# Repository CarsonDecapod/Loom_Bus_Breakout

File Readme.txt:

The Bus Breakout is a board for the Loom Prototyping Platform
It connects to one of the top or bottom ports of the Backplane and breaks out the 40 signals to 3.5mm jacks, female pin headers, and vias for test probes.

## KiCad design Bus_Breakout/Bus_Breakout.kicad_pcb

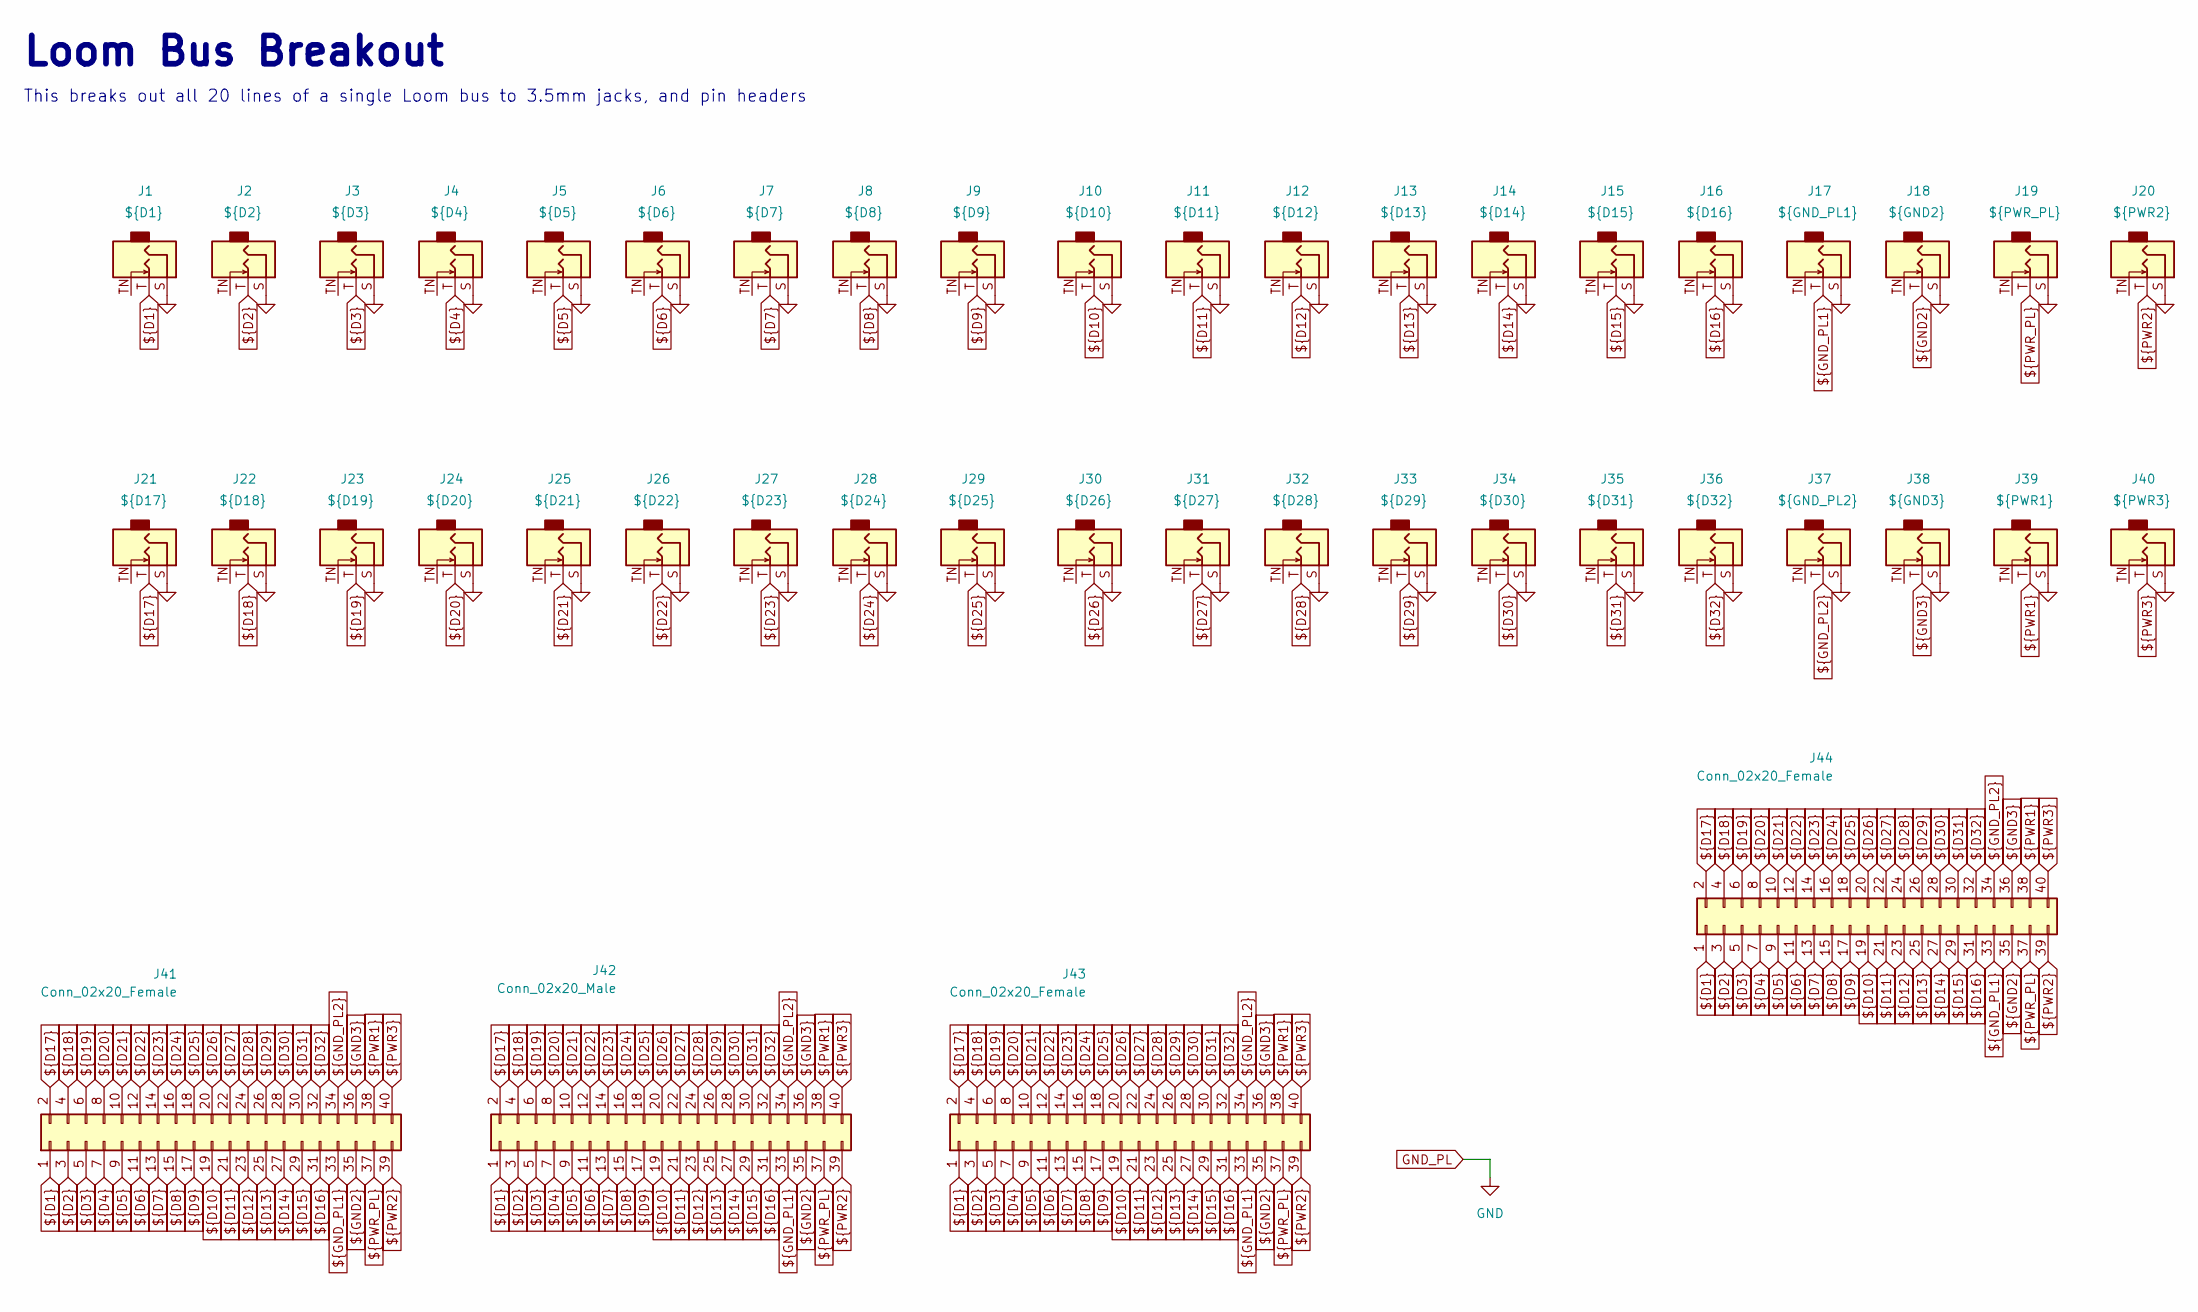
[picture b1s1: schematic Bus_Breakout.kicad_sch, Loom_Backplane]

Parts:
J1, J2, J3, J4, J5, J6, J7, J8, J9, J10, J11, J12, J13, J14, J15, J16, J17, J18, J19, J20, J21, J22, J23, J24, J25, J26, J27, J28, J29, J30, J31, J32, J33, J34, J35, J36, J37, J38, J39, J40: AudioJack2_SwitchT; AudioJack_WQP518MA_Compact_S_LongPads
J41: Conn_02x20_Female; IDC-Header_2x20_P2.54mm_Horizontal
J42: Conn_02x20_Male; PinSocket_2x20_P2.54mm_Horizontal
J43, J44: Conn_02x20_Female; PinSocket_2x20_P2.54mm_Vertical

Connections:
D1/A1: J1.T, J41.1, J42.1, J43.1, J44.1
D2/A2: J2.T, J41.3, J42.3, J43.3, J44.3
D3/A3: J3.T, J41.5, J42.5, J43.5, J44.5
D4/A4: J4.T, J41.7, J42.7, J43.7, J44.7
D5/A5: J5.T, J41.9, J42.9, J43.9, J44.9
D6/A6: J6.T, J41.11, J42.11, J43.11, J44.11
D7/A7: J7.T, J41.13, J42.13, J43.13, J44.13
D8/A8: J8.T, J41.15, J42.15, J43.15, J44.15
D9/A9: J9.T, J41.17, J42.17, J43.17, J44.17
D10/A10: J10.T, J41.19, J42.19, J43.19, J44.19
D11/A11: J11.T, J41.21, J42.21, J43.21, J44.21
D12/A12: J12.T, J41.23, J42.23, J43.23, J44.23
D13/A13: J13.T, J41.25, J42.25, J43.25, J44.25
D14/A14: J14.T, J41.27, J42.27, J43.27, J44.27
D15/A15: J15.T, J41.29, J42.29, J43.29, J44.29
D16/A16: J16.T, J41.31, J42.31, J43.31, J44.31
D17/A17: J21.T, J41.2, J42.2, J43.2, J44.2
D18/A18: J22.T, J41.4, J42.4, J43.4, J44.4
D19/A19: J23.T, J41.6, J42.6, J43.6, J44.6
D20/A20: J24.T, J41.8, J42.8, J43.8, J44.8
D21/A21: J25.T, J41.10, J42.10, J43.10, J44.10
D22/A22: J26.T, J41.12, J42.12, J43.12, J44.12
D23/A23: J27.T, J41.14, J42.14, J43.14, J44.14
D24/A24: J28.T, J41.16, J42.16, J43.16, J44.16
D25/A25: J29.T, J41.18, J42.18, J43.18, J44.18
D26/A26: J30.T, J41.20, J42.20, J43.20, J44.20
D27/A27: J31.T, J41.22, J42.22, J43.22, J44.22
D28/A28: J32.T, J41.24, J42.24, J43.24, J44.24
D29/A29: J33.T, J41.26, J42.26, J43.26, J44.26
D30/A30: J34.T, J41.28, J42.28, J43.28, J44.28
D31/A31: J35.T, J41.30, J42.30, J43.30, J44.30
D32/A32: J36.T, J41.32, J42.32, J43.32, J44.32
GND2/4: J18.T, J41.35, J42.35, J43.35, J44.35
GND3/5: J38.T, J41.36, J42.36, J43.36, J44.36
PWR1/APWR2: J39.T, J41.38, J42.38, J43.38, J44.38
PWR2/APWR3: J20.T, J41.39, J42.39, J43.39, J44.39
PWR3/APWR4: J40.T, J41.40, J42.40, J43.40, J44.40
PWR_PL/APWR1: J19.T, J41.37, J42.37, J43.37, J44.37

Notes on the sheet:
This breaks out all 20 lines of a single Loom bus to 3.5mm jacks, and pin headers
Loom Bus Breakout

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
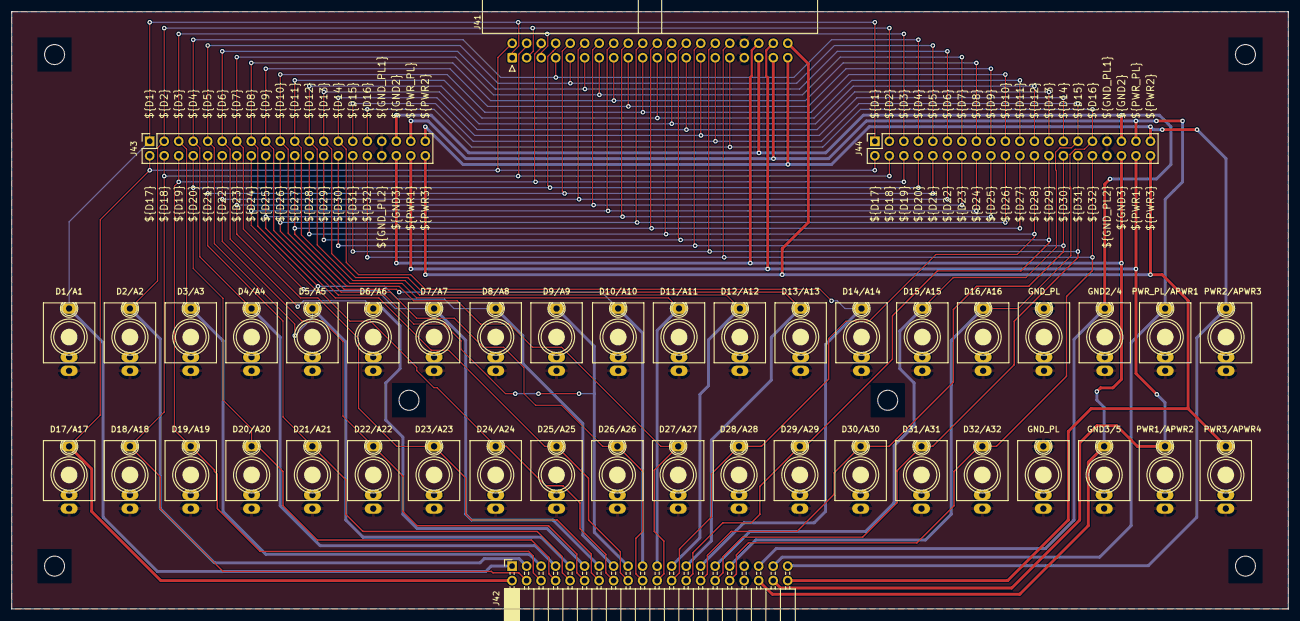
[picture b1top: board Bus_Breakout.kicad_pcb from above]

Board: 2 copper layers, 223.5 x 104.6 mm, 44 parts (0 on the bottom side), 39 nets.

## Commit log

2024-07-07 Bus breakout layed out, ready for routing
2024-07-07 edited readme
2024-07-07 Board Routed and Passing DRC. Still need some cleanup
2024-07-07 Board Routed and Passing DRC.Should be about ready to order
2024-08-13 Bus Breakout Almost ready to order?
2024-08-22 Loom Bus Breakout V1 Ordered
